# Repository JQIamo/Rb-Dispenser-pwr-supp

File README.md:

# Rb-Dispenser-pwr-supp
Power supply for rubidium dispenser.

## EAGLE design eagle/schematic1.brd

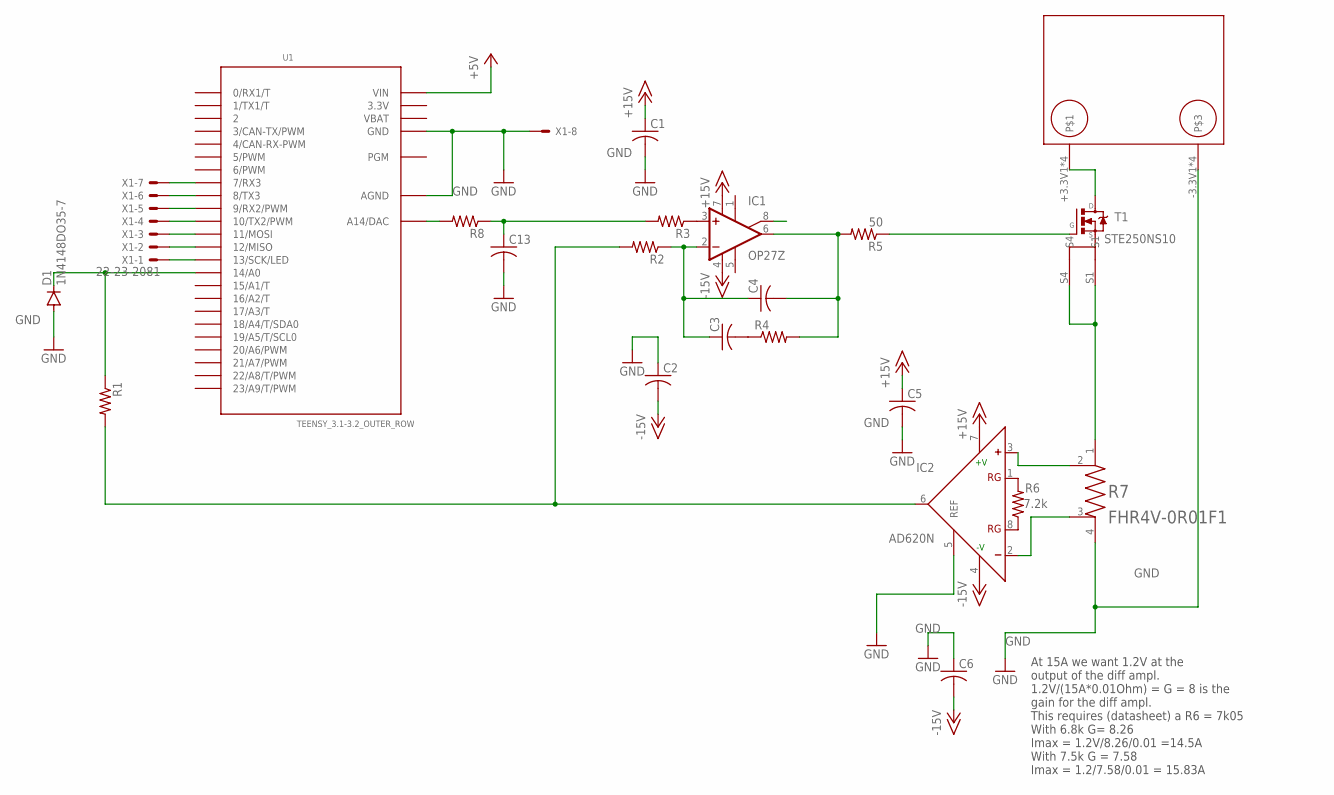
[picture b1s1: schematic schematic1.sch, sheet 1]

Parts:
C1, C2, C3, C4, C5, C6, C13: C-US025-024X044; C025-024X044
D1: 1N4148DO35-7; DO35-7
IC1: OP27Z; DIL08
IC2: AD620N; DIL08
J1: MOLEX_0399200502; 3.3V_HOOKIN
R1, R2, R3, R4, R8: R-US_0204/7; 0204/7
R5: 50; 0204/7
R6: 7.2k; 0204/7
R7: FHR4V-0R01F1; RIEDON_FHR4V-0R1F1
T1: STE250NS10
U1: TEENSY_3.1-3.2_OUTER_ROW; TEENSY_3.0-3.2&LC_OUTER_ROW
X1: 22-23-2081; DIGIKEY ED10566-ND

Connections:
3.3V: U1.3.3V, U1.3.3V1 (3.3V)
+5V: U1.VIN; also elsewhere on the board
+15V: C1.1, C5.1, IC1.7 (V+), IC2.7 (+V); also elsewhere on the board
-15V: C2.2, C6.2, IC1.4 (V-), IC2.4 (-V); also elsewhere on the board
GND: C1.2, C2.1, C5.2, C6.1, C13.2, D1.A, IC2.5 (REF), J1.-3.3V1, J1.-3.3V2, J1.-3.3V3, J1.-3.3V4, R7.4, U1.AGND, U1.GND, U1.GND1 (GND), X1.8; also elsewhere on the board
unnamed: U1.7 (7/RX3), X1.7
unnamed: J1.+3.3V1, J1.+3.3V2, J1.+3.3V3, J1.+3.3V4, T1.D
unnamed: D1.C, R1.1, U1.14/A0
unnamed: IC2.1 (RG), R6.2
unnamed: IC2.8 (RG), R6.1
unnamed: U1.8 (8/TX3), X1.6
unnamed: IC2.6 (OUT), R1.2, R2.2
unnamed: C3.1, C4.1, IC1.2 (-IN), R2.1
unnamed: IC1.3 (+IN), R3.1
unnamed: R8.2, U1.RESET/DAC (A14/DAC)
unnamed: C4.2, IC1.6 (OUT), R4.2, R5.2
unnamed: R5.1, T1.G
unnamed: C3.2, R4.1
unnamed: C13.1, R3.2, R8.1
unnamed: U1.9 (9/RX2/PWM), X1.5
unnamed: R7.1, T1.S1, T1.S4
unnamed: IC2.3 (+), R7.2
unnamed: IC2.2 (-), R7.3
unnamed: U1.10 (10/TX2/PWM), X1.4
unnamed: U1.11 (11/MOSI), X1.3
unnamed: U1.12 (12/MISO), X1.2
unnamed: U1.13 (13/SCK/LED), X1.1
VBAT: U1.VBAT

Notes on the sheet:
At 15A we want 1.2V at the output of the diff ampl. 1.2V/(15A*0.01Ohm) = G = 8 is the gain for the diff ampl. This requires (datasheet) a R6 = 7k05 With 6.8k G= 8.26 Imax = 1.2V/8.26/0.01 =14.5A With 7.5k G = 7.58 Imax = 1.2/7.58/0.01 = 15.83A

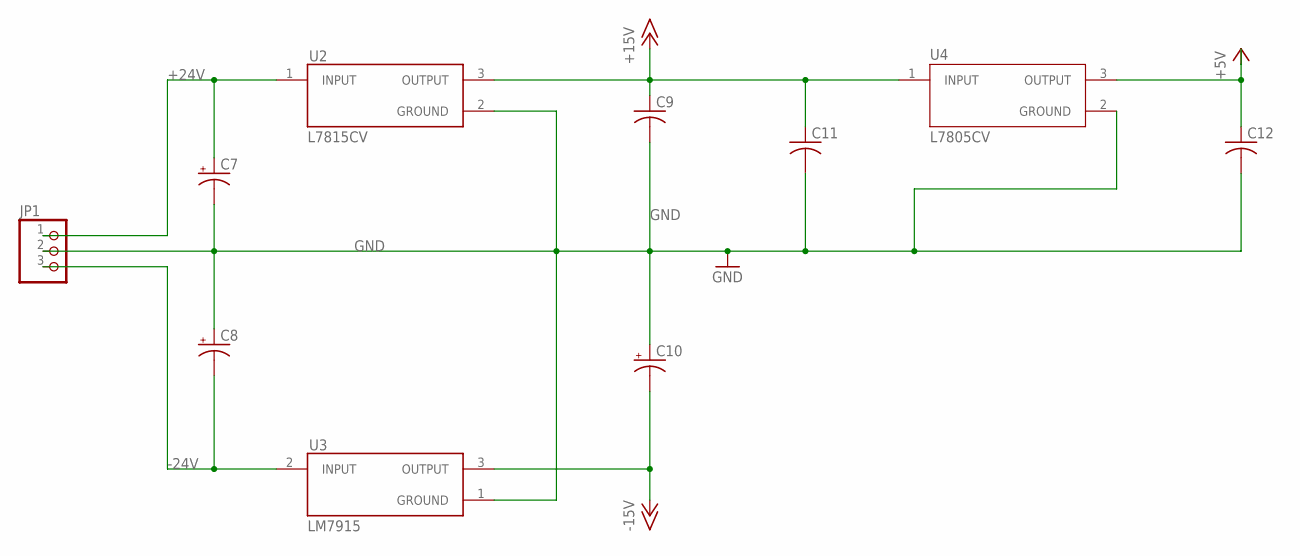
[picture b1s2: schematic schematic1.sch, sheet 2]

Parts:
C7, C8, C10: CPOL-USTT2D4; TT2D4
C9, C11, C12: C-US025-024X044; C025-024X044
JP1: PINHD-1X3; 1X03
U2: L7815CV; TO255P1040X460X1935-3
U3: LM7915; TO255P1040X460X1935-3
U4: L7805CV; TO255P1040X460X1968-3

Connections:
+5V: C12.1, U4.3 (OUTPUT); also elsewhere on the board
+15V: C9.1, C11.1, U2.3 (OUTPUT), U4.1 (INPUT); also elsewhere on the board
+24V: C7.+, JP1.1, U2.1 (INPUT)
-15V: C10.-, U3.3 (OUTPUT); also elsewhere on the board
-24V: C8.-, JP1.3, U3.2 (INPUT)
GND: C7.-, C8.+, C9.2, C10.+, C11.2, C12.2, JP1.2, U2.2 (GROUND), U3.1 (GROUND), U4.2 (GROUND); also elsewhere on the board

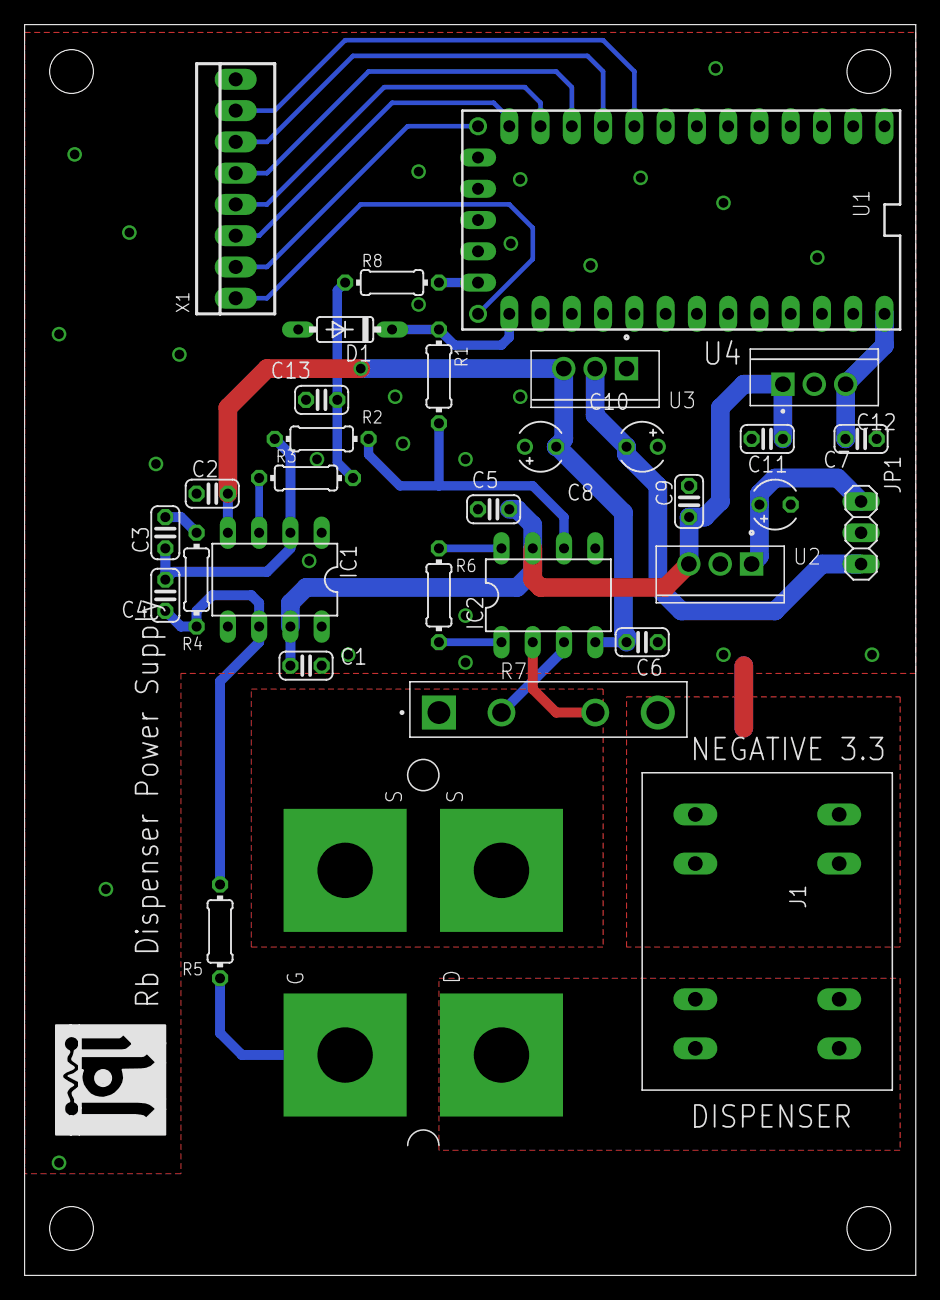
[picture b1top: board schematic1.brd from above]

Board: 2 copper layers, 72.4 x 101.6 mm, 33 parts (0 on the bottom side), 29 nets.

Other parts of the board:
LOGO1: JQI-LOGOSILK; JQI_LOGO_NEGATIVE-SILKSCREEN

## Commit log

2020-10-29 added eagle design
2020-10-29 Fixed MOS package - H and V dim are different - Holes are M4 and not M6
2020-10-29 Fixed wrong pinout for negative regulator - This is a classic error that often goes unnoticed. TO2020 Negative regulators have the pinout: 1-GND 2-INPUT 3-OUTPUT This is different from positive regul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
2020-10-30 Removed resistor reordered parts and added LPF
    - Resistor from pin 1 and 8 of OP27 is a mistake and it was removed.
    - Components name re-ordered and re-assigned
    - RC filter added after Teensy DAC. It might be necessary to filter
    out digital interference (especially from USB port)
2020-11-10 Changed value of sensing resistor to 0.01Ohm and added value for R6 TO DO: 1 - Add missing values for resistors and capacitors according with the prototype board 2 - Fix the hole size for the large 3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
2020-11-11 added code example for arduino
